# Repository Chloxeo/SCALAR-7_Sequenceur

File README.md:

# SCALAR-7 : Sequenceur Bas

Sequencer board of the **lower stage** of **SCALAR-7**, a two-stage rocket launched at **C'Space 2026**.
It handles the lower stage's flight events: lift-off detection, stage separation through the **SSIE** motor, separation detection and parachute deployment.

---
## Table of contents

- [Board features](#board-features)
- [Architecture](#architecture)
  - [Power supply](#power-supply)
  - [Microcontroller](#microcontroller)
  - [Stage separation](#stage-separation)
  - [Parachute](#parachute)
  - [Sensors](#sensors)
  - [HMI connection](#hmi-connection)
- [Main components](#main-components)
- [Repository structure](#repository-structure)

---

## Board features

| Function | Implementation |
|---|---|
| Processing / sequencing | Raspberry Pi **Pico** (RP2040) |
| Lift-off detection | Connector for the lift-off detection lug |
| Stage separation | **DRV8874** H-bridge driving the SSIE DC motor (12 V), with current sensing and fault output |
| SSIE position | Connector for two end-stop switches (open / closed) |
| Separation detection | Jack (with Schmitt trigger filtering) or push button, on a shared connector |
| Parachute | Servo connector (6 V) |
| Flight measurements | **WitMotion WT901B** inertial measurement unit (UART, I²C optional) |
| Power supply | 4S battery, protected input (reverse polarity, overcurrent), 3.3 V, 5 V, 6 V and 12 V regulators |
| HMI interface | D-Sub 15 connector: power switch, jack, status LED, manual commands, debug UART and SWD, rail status LEDs |
| Indicators | Buzzer, power LED |

---

## Architecture

```mermaid
flowchart LR
    BAT[4S battery<br/>J1] --> IHM[HMI connector<br/>D-Sub 15]
    IHM -- VBATT_ihm --> PROT[Reverse-polarity P-MOS<br/>+ polyfuse]
    PROT --> REG33[LD1117 3V3]
    PROT --> REG5[L7805 5V]
    PROT --> REG6[NJM7806 6V]
    PROT --> REG12[L7812 12V]

    REG5 --> PICO[Raspberry Pi Pico]
    IHM -- ALIM_DEBUG --> PICO
    REG12 --> DRV[DRV8874<br/>H-bridge]
    DRV --> MOT[SSIE motor]
    REG6 --> SERVO[Parachute servo]
    REG5 --> IMU[WT901B<br/>IMU]
    REG5 --> BUZ[Buzzer]

    PICO -- EN / PH --> DRV
    DRV -- CS / nFAULT --> PICO
    ENDSTOP[SSIE end-stops] --> PICO
    SEP[Separation jack / button] --> PICO
    COSSE[Lift-off lug] --> PICO
    PICO --> SERVO
    IMU <-- UART --> PICO
    IHM <-- jack / buttons / LED / UART / SWD --> PICO
```

### Power supply

The board is powered by a **4S** battery. The supply goes through the HMI before coming back to the board, so the sequencer is switched on from the outside. The input is protected against reverse polarity (P-MOSFET) and overcurrent (polyfuse), then four linear regulators generate the **3V3** (logic), **5V** (Pico, IMU, buzzer), **6V** (parachute servo) and **12V** (SSIE motor) rails.

### Microcontroller

A **Raspberry Pi Pico** runs the flight sequence: it reads the detection inputs and the IMU, then drives the SSIE motor and the parachute servo. It is mounted on two pin headers that also serve as test points. Its VSYS input is supplied either by the board's 5V rail or by the HMI debug supply through two diodes, so it can be programmed without the battery.

### Stage separation

- **SSIE motor**: a **DRV8874** H-bridge (PH/EN mode) drives the separation DC motor from the 12V rail. The Pico controls its direction and enable, and reads back the motor current (ADC) and the fault output.
- **SSIE position**: two end-stop switches mounted on the SSIE shaft tell the Pico when the mechanism is fully open or fully closed.
- **Separation detection**: the separation can be detected either by a jack, filtered by an RC network and a Schmitt trigger, or by a push button. Both share the same connector, so only one of them needs to be wired.

### Parachute

A servo connector, powered from the 6V rail, deploys the parachute.

### Sensors

- **Lift-off detection**: a connector for the lift-off detection lug, read by the Pico with a pull-down resistor.
- **Flight measurements**: **WT901B** inertial measurement unit, connected over UART. It provides accelerations, angular rates, attitude, pressure, altitude and temperature.

### HMI connection

The **D-Sub 15** connector links the board to the HMI. It carries the battery supply (out and back, for switching the board on), the jack, the status LED, the manual parachute and SSIE commands, the Pico's debug UART and SWD, and the four supply rails for the status LEDs on the HMI.

---

## Main components

| Ref. | Component | Function |
|---|---|---|
| — | Raspberry Pi Pico | Microcontroller |
| U5 | TI DRV8874 | H-bridge motor driver |
| IC1 | TI SN74LVC1G17DBVT | Schmitt trigger buffer (separation jack) |
| W1 | WitMotion WT901B | IMU with barometer |
| U1 | ST LD1117DT33TR | 3.3 V regulator |
| U2 | ST L7805CDT-TR | 5 V regulator |
| U3 | NJR NJM7806DL1A | 6 V regulator |
| U4 | ST L7812 | 12 V regulator |
| Q2 | onsemi FDN360P | Reverse-polarity protection |
| F1 | Littelfuse 1210L110/16WR | Polyfuse |
| Q1 | N-MOSFET | Buzzer driver |
| J2 | D-Sub 15 | HMI connection |
| J4 | 4-pin connector | Parachute servo |
| J7 | 2-pin connector | SSIE motor |
| J9 | 4-pin connector | SSIE end-stops |
| J12 | 2-pin connector | Separation detection |

---

## Repository structure

```
SCALAR-7_Sequenceur_Bas/
├── hardware/          # KiCad project
├── images/
├── schematic.pdf
└── README.md
```

---

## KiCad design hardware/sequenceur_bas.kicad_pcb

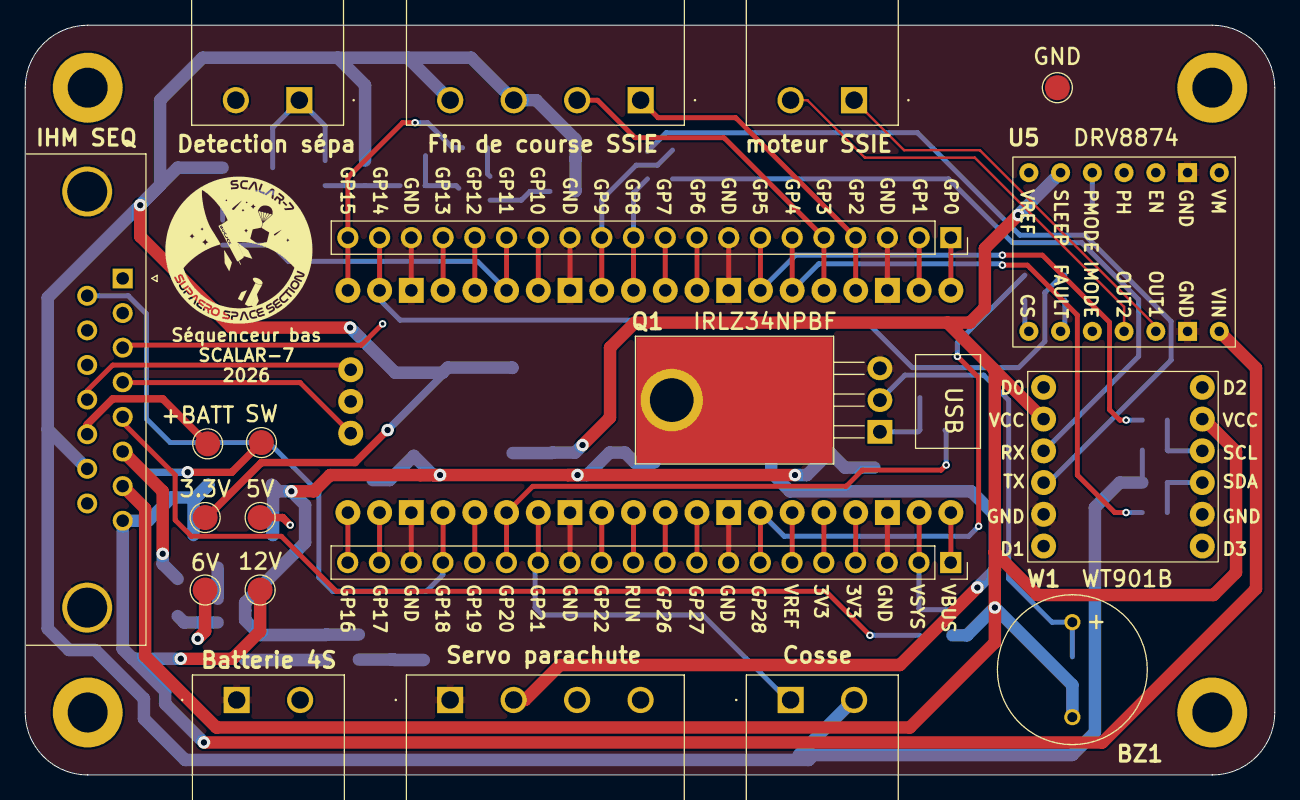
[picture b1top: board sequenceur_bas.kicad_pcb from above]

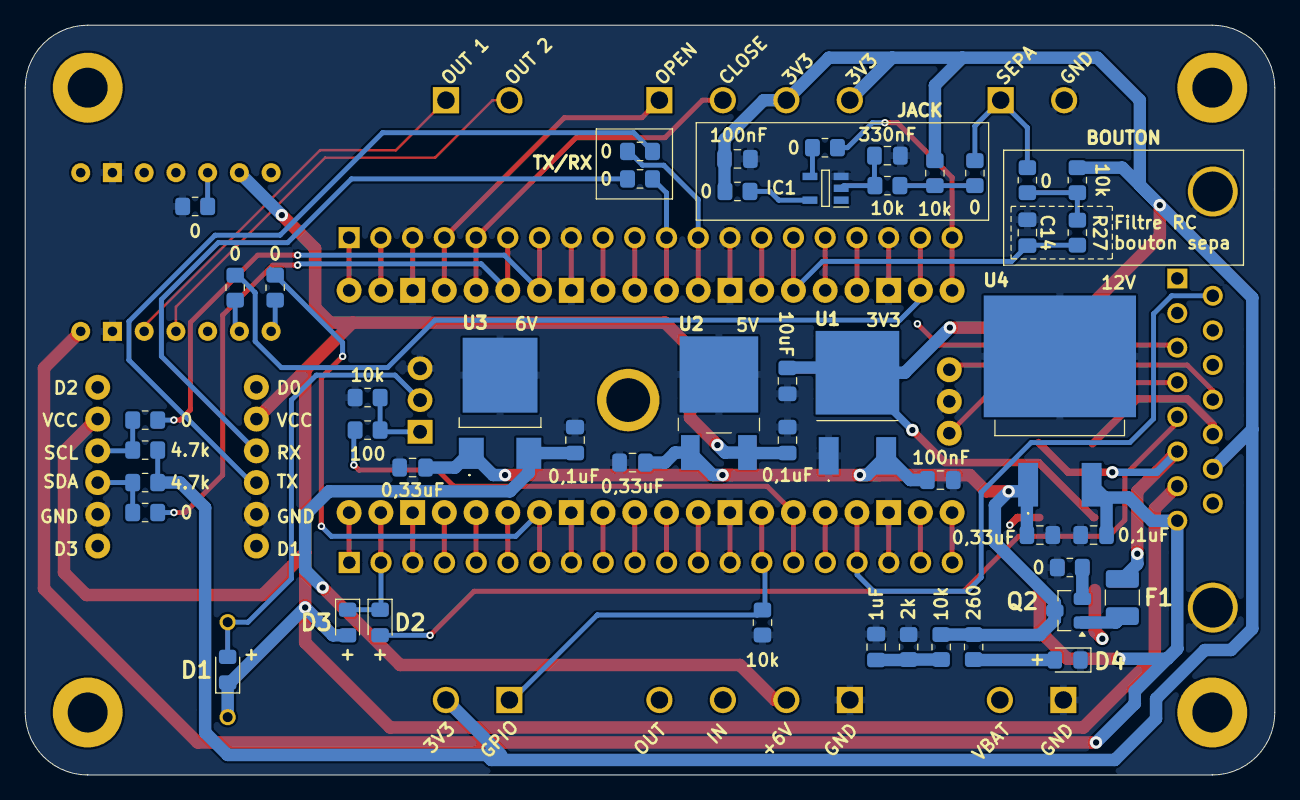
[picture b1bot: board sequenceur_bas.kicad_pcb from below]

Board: 4 copper layers, 100.0 x 60.0 mm, 72 parts (47 on the bottom side), 55 nets.

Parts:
BZ1: Buzzer; KXG1205C
C1: 1uF; C_0805_2012Metric_Pad1.18x1.45mm_HandSolder
C2, C4, C5: 0,33uF; C_0805_2012Metric_Pad1.18x1.45mm_HandSolder
C3, C10: 100nF; C_0805_2012Metric_Pad1.18x1.45mm_HandSolder
C6: 10uF; C_0805_2012Metric_Pad1.18x1.45mm_HandSolder
C7, C8, C9: 0,1uF; C_0805_2012Metric_Pad1.18x1.45mm_HandSolder
C11: 330nF; C_0805_2012Metric_Pad1.18x1.45mm_HandSolder
C14: ?; C_0805_2012Metric_Pad1.18x1.45mm_HandSolder
D1, D2, D3: D; D_0805_2012Metric_Pad1.15x1.40mm_HandSolder
D4: LED; LED_0805_2012Metric_Pad1.15x1.40mm_HandSolder
F1: 1210L110/16WR; Fuse_1210_3225Metric_Pad1.42x2.65mm_HandSolder
H1, H2, H3, H4: MountingHole; MountingHole_3.2mm_M3
IC1: SN74LVC1G17DBVT; SOT95P280X145-5N
J1: Batterie 4S; Bornier_Enfichable_2Pin_5mm_Horizontal
J2: IHM SEQ; DSUB-15_Pins_Horizontal_P2.77x2.84mm_EdgePinOffset4.94mm_Ho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
J3: Cosse; Bornier_Enfichable_2Pin_5mm_Horizontal
J4: Servo parachute; Bornier_Enfichable_4Pin_5mm_Horizontal
J5: PICO
J7: moteur SSIE; Bornier_Enfichable_2Pin_5mm_Horizontal
J9: Fin de course SSIE; Bornier_Enfichable_4Pin_5mm_Horizontal
J10: DEBUG_L; PinSocket_1x20_P2.54mm_Vertical
J11: DEBUG_R; PinSocket_1x20_P2.54mm_Vertical
J12: Detection sépa; Bornier_Enfichable_2Pin_5mm_Horizontal
Q1: IRLZ34NPBF; TO-220-3_Horizontal_TabDown
Q2: FDN360P; SuperSOT-3
R1: 100; R_0805_2012Metric_Pad1.20x1.40mm_HandSolder
R2, R3, R6, R14, R15, R26: 10k; R_0805_2012Metric_Pad1.20x1.40mm_HandSolder
R4, R8, R9, R12, R13, R16, R17, R18, R19, R22, R24, R25: 0; R_0805_2012Metric_Pad1.20x1.40mm_HandSolder
R5: 260; R_0805_2012Metric_Pad1.20x1.40mm_HandSolder
R7: 2k; R_0805_2012Metric_Pad1.20x1.40mm_HandSolder
R10, R11: 4.7k; R_0805_2012Metric_Pad1.20x1.40mm_HandSolder
R27: ?; R_0805_2012Metric_Pad1.20x1.40mm_HandSolder
TP1: +BATT; TestPoint_Pad_D2.0mm
TP2: SW; TestPoint_Pad_D2.0mm
TP3: GND; TestPoint_Pad_D2.0mm
TP5: 3.3V; TestPoint_Pad_D2.0mm
TP6: 5V; TestPoint_Pad_D2.0mm
TP7: 6V; TestPoint_Pad_D2.0mm
TP8: 12V; TestPoint_Pad_D2.0mm
U1: LD1117DT33TR
U2: L7805CDT-TR; L7805CDTTR
U3: NJM7806DL1A; NJM2845DL133TE1
U4: L7812; L7812CD2TTR
U5: DRV8874
W1: WT901B

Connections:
+3.3V: C6.1, C10.2, J2.14, J3.2, J9.3, J9.4, R10.2, R11.2, R14.2, R17.2, R26.2, TP5.1, U1.2 (VO)
+5V: BZ1.2 (-), C7.1, D1.1 (K), D3.2 (A), J2.7, TP6.1, U2.3 (OUT), U5.6 (SLEEP), W1.2 (VCC), W1.8 (VCC)
+6V: C8.1, J2.15, J4.2, TP7.1, U3.3 (OUT)
+12V: C9.1, J2.8, TP8.1, U4.3 (OUT), U5.14 (VIN)
+VBATT: J1.2, J2.13, TP1.1
/Raspberry PICO/BTN_SEP: C14.2, J5.15 (GP11), J10.15, R27.1
/Raspberry PICO/BUZZER: J5.26 (GP20), J11.15, R1.1
/Raspberry PICO/COSSE: J3.1, J5.27 (GP21), J11.14, R3.1
/Raspberry PICO/DEBUG.ALIM_DEBUG: D2.2 (A), J2.5
/Raspberry PICO/DEBUG.RX_PROBE: J2.11 (P111), J5.1 (GP0), J10.1
/Raspberry PICO/DEBUG.SWCLK: J2.4, J5.D1 (SWCLK)
/Raspberry PICO/DEBUG.SWDIO: J2.12, J5.D3 (SWDIO)
/Raspberry PICO/DEBUG.TX_PROBE: J2.3, J5.2 (GP1), J10.2
/Raspberry PICO/IHM.BTN_PARA: J2.2, J5.22 (GP17), J11.19
/Raspberry PICO/IHM.BTN_SSIE: J2.10, J5.21 (GP16), J11.20
/Raspberry PICO/IHM.JACK_SEQ: J2.1, J5.25 (GP19), J11.16
/Raspberry PICO/IHM.LED_ETAT: J2.9, J5.24 (GP18), J11.17
/Raspberry PICO/JACK_SEP: J5.20 (GP15), J10.20, R16.2
/Raspberry PICO/SERVO_PARA.INPUT: J4.3, J5.29 (GP22), J11.12
/Raspberry PICO/SERVO_PARA.OUTPUT: J4.4, J5.31 (GP26_A0), J11.10
/Raspberry PICO/SSIE pont-H enable: J5.16 (GP12), J10.16, U5.3 (EN/IN1)
/Raspberry PICO/SSIE pont-H phase: J5.17 (GP13), J10.17, U5.4 (PH/IN2)
/Raspberry PICO/SW_CLOSE_SSIE: J5.5 (GP3), J9.2, J10.5
/Raspberry PICO/SW_OPEN_SSIE: J5.4 (GP2), J9.1, J10.4
/Raspberry PICO/WITMOTION.RX_WT: J5.11 (GP8), J10.11, R8.1
/Raspberry PICO/WITMOTION.SCL: J5.7 (GP5), J10.7, R12.2
/Raspberry PICO/WITMOTION.SDA: J5.6 (GP4), J10.6, R13.1
/Raspberry PICO/WITMOTION.TX_WT: J5.12 (GP9), J10.12, R9.2
/Raspberry PICO/cs_motor: J5.34 (GP28_A2), J11.7, R18.2
/Raspberry PICO/nF_motor: J5.19 (GP14), J10.19, R22.2
/SEPARATION/BTN_BRUT: R24.2, R26.1, R27.2
/SEPARATION/JACK_BRUT: R14.1, R15.1, R25.2
GND: C1.2, C2.2, C3.2, C4.2, C5.2, C6.2, C7.2, C8.2, C9.2, C10.1, C11.1, C14.1, D4.1 (K), IC1.3 (GND), J1.1, J2.0, J4.1, J5.3 (GND_1), J5.8 (GND_2), J5.13 (GND_3), J5.18 (GND_4), J5.23 (GND_5), J5.28 (GND_6), J5.33 (GND_7), J5.38 (GND_8), J5.D2 (GND_9), J10.3, J10.8, J10.13, J10.18, J11.3, J11.8, J11.13, J11.18, J12.2, Q1.3 (S), R2.2, R3.2, R4.2, R7.2, R19.2, TP3.1, U1.1 (GND), U2.2 (GND), U3.2 (GND), U4.2 (GND), U5.2 (GND), U5.13 (GND), W1.5 (GND), W1.11 (GND)
unnamed: BZ1.1 (+), D1.2 (A), Q1.2 (D)
unnamed: C1.1, R6.2, R7.1
unnamed: D2.1 (K), D3.1 (K), J5.39 (VSYS), J11.2
unnamed: D4.2 (A), R5.2
unnamed: C11.2, IC1.2 (A), R15.2
unnamed: IC1.5 (VCC), R17.1
unnamed: IC1.4 (Y), R16.1
unnamed: J7.1, U5.12 (OUT1)
unnamed: J7.2, U5.11 (OUT2)
unnamed: J12.1, R24.1, R25.1
unnamed: Q1.1 (G), R1.2, R2.1
unnamed: F1.2, Q2.1 (D)
unnamed: Q2.2 (G), R4.1
unnamed: C2.1, C3.1, C4.1, C5.1, Q2.3 (S), R5.1, R6.1, U1.3 (VI), U2.1 (IN), U3.1 (IN), U4.1 (IN)
unnamed: R18.1, U5.8 (CS)
unnamed: R22.1, U5.9 (FAULT)
unnamed: R19.1, U5.5 (PMODE)
unnamed: R8.2, W1.3 (RX)
unnamed: R10.1, R12.1, W1.9 (SCL)
unnamed: R11.1, R13.2, W1.10 (SDA)
unnamed: R9.1, W1.4 (TX)
VBATT_ihm: F1.1, J2.6, TP2.1
